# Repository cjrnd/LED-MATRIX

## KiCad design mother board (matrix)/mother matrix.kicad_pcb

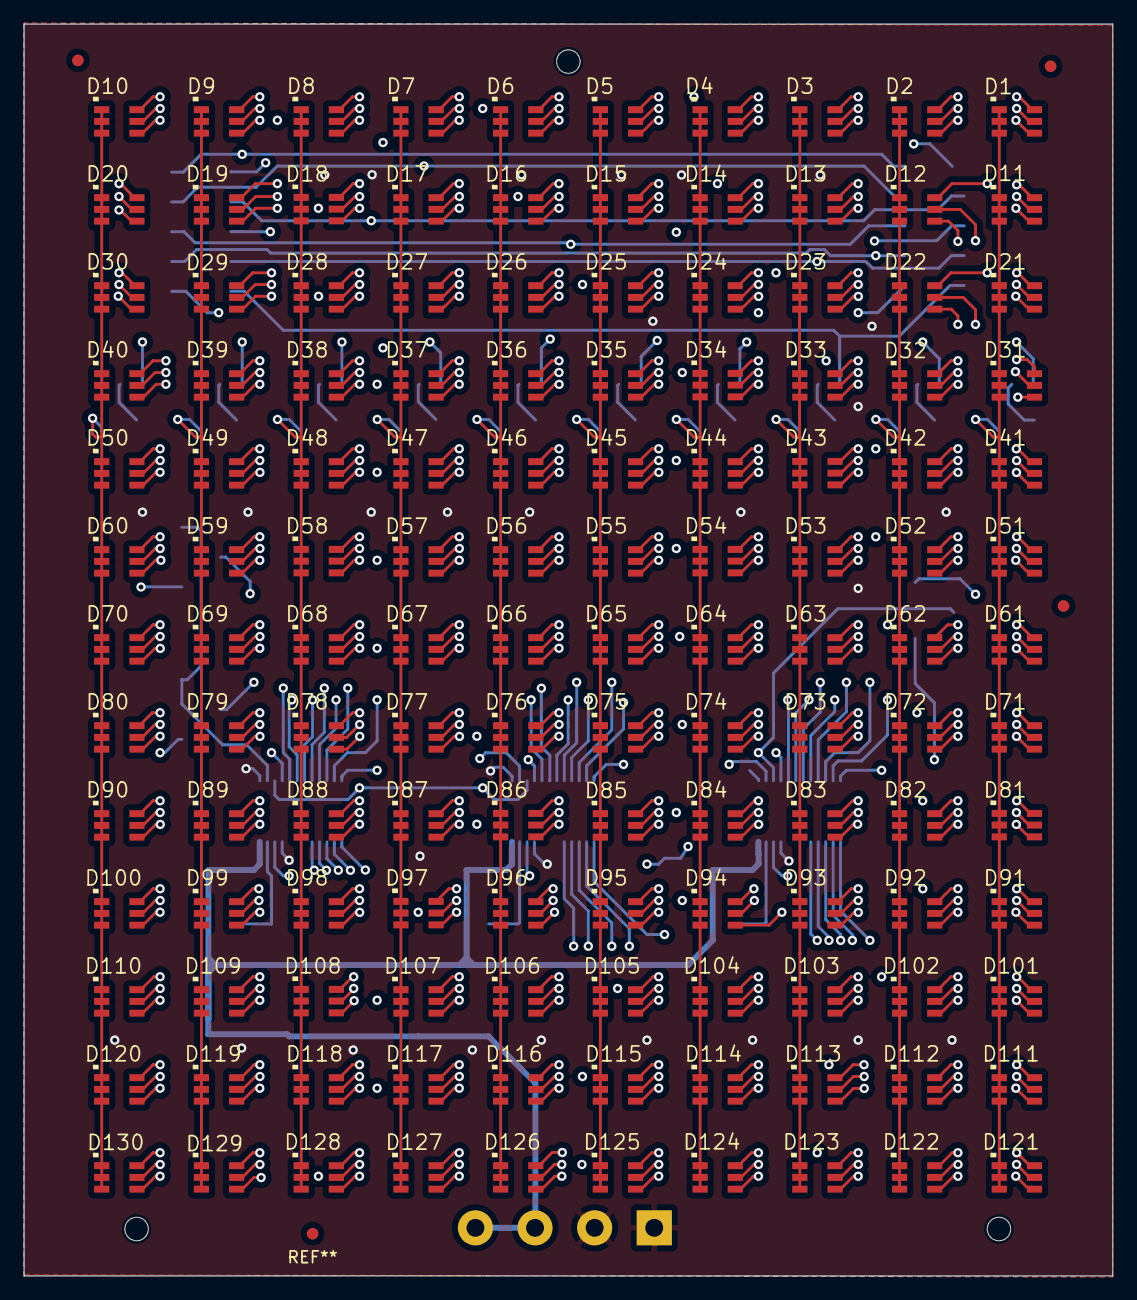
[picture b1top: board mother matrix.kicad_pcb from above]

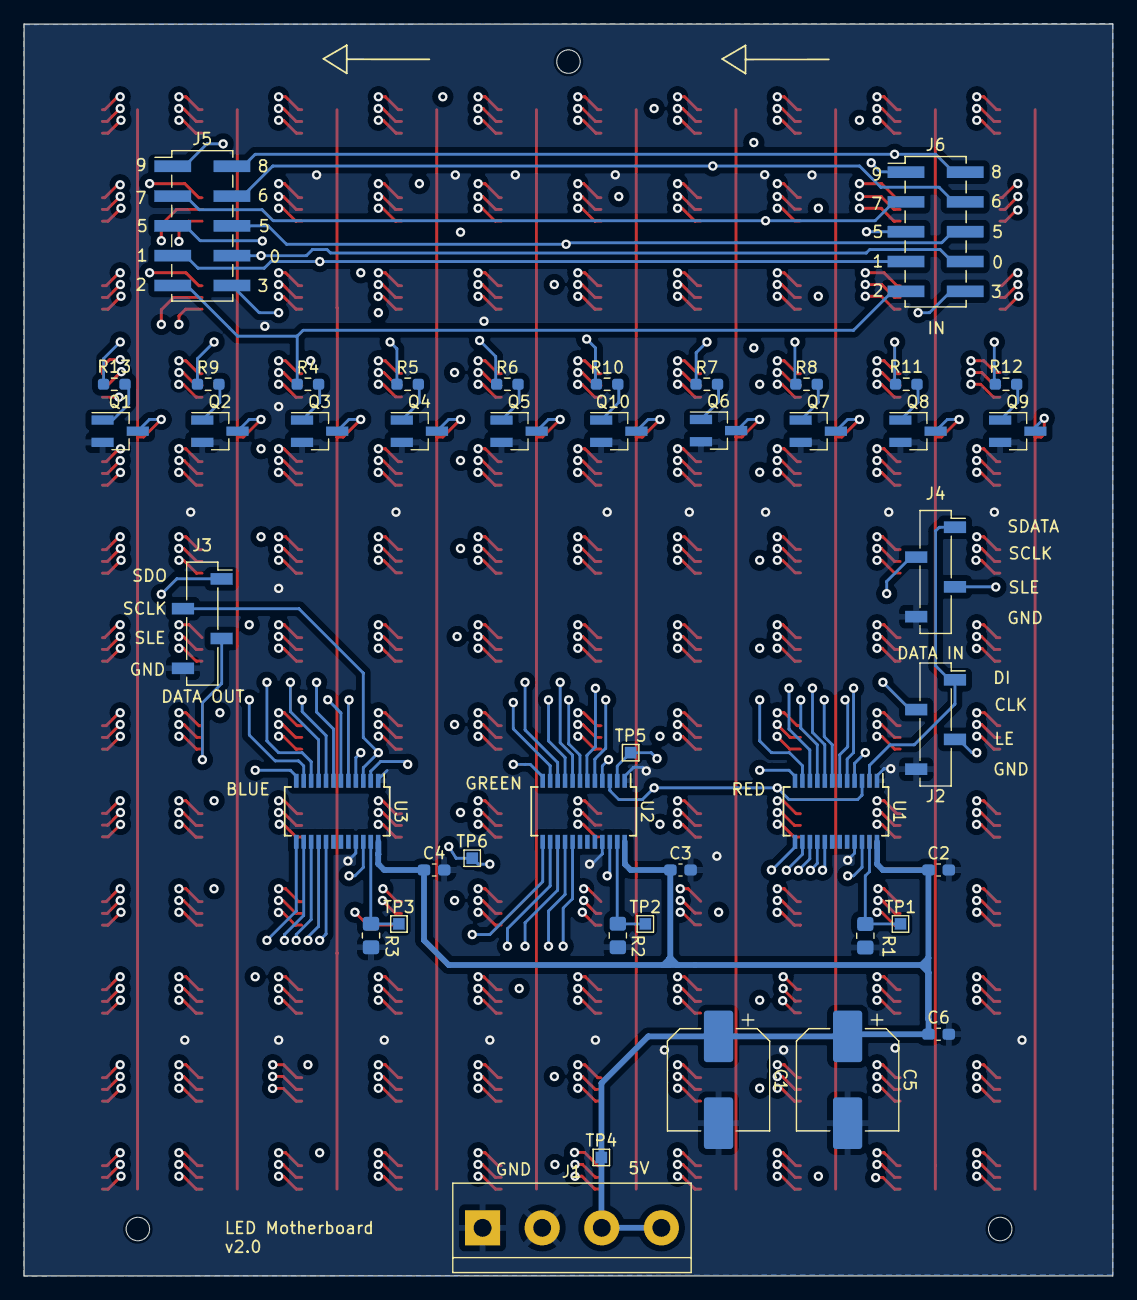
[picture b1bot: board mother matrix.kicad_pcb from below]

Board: 4 copper layers, 92.8 x 106.7 mm, 174 parts (44 on the bottom side), 80 nets.

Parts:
C1, C5: 220u; CP_Elec_8x10.5
C2, C3, C4, C6: 100n; C_0603_1608Metric_Pad1.08x0.95mm_HandSolder
D1, D2, D3, D4, D5, D6, D7, D8, D9, D10, D11, D12, D13, D14, D15, D16, D17, D18, D19, D20, D21, D22, D23, D24, D25, D26, D27, D28, D29, D30, D31, D32, D33, D34, D35, D36, D37, D38, D39, D40, D41, D42, D43, D44, D45, D46, D47, D48, D49, D50, D51, D52, D53, D54, D55, D56, D57, D58, D59, D60, D61, D62, D63, D64, D65, D66, D67, D68, D69, D70, D71, D72, D73, D74, D75, D76, D77, D78, D79, D80, D81, D82, D83, D84, D85, D86, D87, D88, D89, D90, D91, D92, D93, D94, D95, D96, D97, D98, D99, D100, D101, D102, D103, D104, D105, D106, D107, D108, D109, D110, D111, D112, D113, D114, D115, D116, D117, D118, D119, D120, D121, D122, D123, D124, D125, D126, D127, D128, D129, D130: LED_RGB; 3535_PLCC6
J1: POWER; TerminalBlock_bornier-4_P5.08mm
J2: DATA IN; PinSocket_1x04_P2.54mm_Vertical_SMD_Pin1Right
J3: DATA OUT; PinSocket_1x04_P2.54mm_Vertical_SMD_Pin1Right
J4: Serial_BUS; PinSocket_1x04_P2.54mm_Vertical_SMD_Pin1Right
J5: OUTPUT; PinHeader_2x05_P2.54mm_Vertical_SMD
J6: INPUT; PinHeader_2x05_P2.54mm_Vertical_SMD
Q1, Q2, Q3, Q4, Q5, Q6, Q7, Q8, Q9, Q10: PMV45EN2R; SOT-23_Handsoldering
R1: R_red; R_0805_2012Metric_Pad1.20x1.40mm_HandSolder
R2: R_green; R_0805_2012Metric_Pad1.20x1.40mm_HandSolder
R3: R_blue; R_0805_2012Metric_Pad1.20x1.40mm_HandSolder
R4, R5, R6, R7, R8, R9, R10, R11, R12, R13: 100; R_0603_1608Metric_Pad0.98x0.95mm_HandSolder
TP1, TP2, TP3, TP4, TP5, TP6: TestPoint; TestPoint_Pad_1.0x1.0mm
U1, U2, U3: SM16206; SSOP-24_3.9x8.7mm_P0.635mm

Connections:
+5V: C1.1, C2.1, C3.1, C4.1, C5.1, C6.1, J1.3, J1.4, TP4.1, U1.24 (VDD), U2.24 (VDD), U3.24 (VDD)
/Led/B_Row0: D1.4 (RA), D2.4 (RA), D3.4 (RA), D4.4 (RA), D5.4 (RA), D6.4 (RA), D7.4 (RA), D8.4 (RA), D9.4 (RA), D10.4 (RA), U3.5 (OUT0)
/Led/B_Row1: D11.4 (RA), D12.4 (RA), D13.4 (RA), D14.4 (RA), D15.4 (RA), D16.4 (RA), D17.4 (RA), D18.4 (RA), D19.4 (RA), D20.4 (RA), U3.6 (OUT1)
/Led/B_Row2: D21.4 (RA), D22.4 (RA), D23.4 (RA), D24.4 (RA), D25.4 (RA), D26.4 (RA), D27.4 (RA), D28.4 (RA), D29.4 (RA), D30.4 (RA), U3.7 (OUT2)
/Led/B_Row3: D31.4 (RA), D32.4 (RA), D33.4 (RA), D34.4 (RA), D35.4 (RA), D36.4 (RA), D37.4 (RA), D38.4 (RA), D39.4 (RA), D40.4 (RA), U3.8 (OUT3)
/Led/B_Row4: D41.4 (RA), D42.4 (RA), D43.4 (RA), D44.4 (RA), D45.4 (RA), D46.4 (RA), D47.4 (RA), D48.4 (RA), D49.4 (RA), D50.4 (RA), U3.9 (OUT4)
/Led/B_Row5: D51.4 (RA), D52.4 (RA), D53.4 (RA), D54.4 (RA), D55.4 (RA), D56.4 (RA), D57.4 (RA), D58.4 (RA), D59.4 (RA), D60.4 (RA), U3.10 (OUT5)
/Led/B_Row6: D61.4 (RA), D62.4 (RA), D63.4 (RA), D64.4 (RA), D65.4 (RA), D66.4 (RA), D67.4 (RA), D68.4 (RA), D69.4 (RA), D70.4 (RA), U3.11 (OUT6)
/Led/B_Row7: D71.4 (RA), D72.4 (RA), D73.4 (RA), D74.4 (RA), D75.4 (RA), D76.4 (RA), D77.4 (RA), D78.4 (RA), D79.4 (RA), D80.4 (RA), U3.12 (OUT7)
/Led/B_Row8: D81.4 (RA), D82.4 (RA), D83.4 (RA), D84.4 (RA), D85.4 (RA), D86.4 (RA), D87.4 (RA), D88.4 (RA), D89.4 (RA), D90.4 (RA), U3.13 (OUT8)
/Led/B_Row9: D91.4 (RA), D92.4 (RA), D93.4 (RA), D94.4 (RA), D95.4 (RA), D96.4 (RA), D97.4 (RA), D98.4 (RA), D99.4 (RA), D100.4 (RA), U3.14 (OUT9)
/Led/B_Row10: D101.4 (RA), D102.4 (RA), D103.4 (RA), D104.4 (RA), D105.4 (RA), D106.4 (RA), D107.4 (RA), D108.4 (RA), D109.4 (RA), D110.4 (RA), U3.15 (OUT10)
/Led/B_Row11: D111.4 (RA), D112.4 (RA), D113.4 (RA), D114.4 (RA), D115.4 (RA), D116.4 (RA), D117.4 (RA), D118.4 (RA), D119.4 (RA), D120.4 (RA), U3.16 (OUT11)
/Led/B_Row12: D121.4 (RA), D122.4 (RA), D123.4 (RA), D124.4 (RA), D125.4 (RA), D126.4 (RA), D127.4 (RA), D128.4 (RA), D129.4 (RA), D130.4 (RA), U3.17 (OUT12)
/Led/Col0: J5.8, J6.8, R13.1
/Led/Col1: J5.7, J6.7, R9.1
/Led/Col2: J5.9, J6.9, R4.1
/Led/Col3: J5.10, J6.10, R5.1
/Led/Col4: J5.5, J6.5, R6.1
/Led/Col5: J5.6, J6.6, R10.1
/Led/Col6: J5.4, J6.4, R7.1
/Led/Col7: J5.3, J6.3, R8.1
/Led/Col8: J5.2, J6.2, R11.2
/Led/Col9: J5.1, J6.1, R12.2
/Led/G_Row0: D1.5 (GA), D2.5 (GA), D3.5 (GA), D4.5 (GA), D5.5 (GA), D6.5 (GA), D7.5 (GA), D8.5 (GA), D9.5 (GA), D10.5 (GA), U2.5 (OUT0)
/Led/G_Row1: D11.5 (GA), D12.5 (GA), D13.5 (GA), D14.5 (GA), D15.5 (GA), D16.5 (GA), D17.5 (GA), D18.5 (GA), D19.5 (GA), D20.5 (GA), U2.6 (OUT1)
/Led/G_Row2: D21.5 (GA), D22.5 (GA), D23.5 (GA), D24.5 (GA), D25.5 (GA), D26.5 (GA), D27.5 (GA), D28.5 (GA), D29.5 (GA), D30.5 (GA), U2.7 (OUT2)
/Led/G_Row3: D31.5 (GA), D32.5 (GA), D33.5 (GA), D34.5 (GA), D35.5 (GA), D36.5 (GA), D37.5 (GA), D38.5 (GA), D39.5 (GA), D40.5 (GA), U2.8 (OUT3)
/Led/G_Row4: D41.5 (GA), D42.5 (GA), D43.5 (GA), D44.5 (GA), D45.5 (GA), D46.5 (GA), D47.5 (GA), D48.5 (GA), D49.5 (GA), D50.5 (GA), U2.9 (OUT4)
/Led/G_Row5: D51.5 (GA), D52.5 (GA), D53.5 (GA), D54.5 (GA), D55.5 (GA), D56.5 (GA), D57.5 (GA), D58.5 (GA), D59.5 (GA), D60.5 (GA), U2.10 (OUT5)
/Led/G_Row6: D61.5 (GA), D62.5 (GA), D63.5 (GA), D64.5 (GA), D65.5 (GA), D66.5 (GA), D67.5 (GA), D68.5 (GA), D69.5 (GA), D70.5 (GA), U2.11 (OUT6)
/Led/G_Row7: D71.5 (GA), D72.5 (GA), D73.5 (GA), D74.5 (GA), D75.5 (GA), D76.5 (GA), D77.5 (GA), D78.5 (GA), D79.5 (GA), D80.5 (GA), U2.12 (OUT7)
/Led/G_Row8: D81.5 (GA), D82.5 (GA), D83.5 (GA), D84.5 (GA), D85.5 (GA), D86.5 (GA), D87.5 (GA), D88.5 (GA), D89.5 (GA), D90.5 (GA), U2.13 (OUT8)
/Led/G_Row9: D91.5 (GA), D92.5 (GA), D93.5 (GA), D94.5 (GA), D95.5 (GA), D96.5 (GA), D97.5 (GA), D98.5 (GA), D99.5 (GA), D100.5 (GA), U2.14 (OUT9)
/Led/G_Row10: D101.5 (GA), D102.5 (GA), D103.5 (GA), D104.5 (GA), D105.5 (GA), D106.5 (GA), D107.5 (GA), D108.5 (GA), D109.5 (GA), D110.5 (GA), U2.15 (OUT10)
/Led/G_Row11: D111.5 (GA), D112.5 (GA), D113.5 (GA), D114.5 (GA), D115.5 (GA), D116.5 (GA), D117.5 (GA), D118.5 (GA), D119.5 (GA), D120.5 (GA), U2.16 (OUT11)
/Led/G_Row12: D121.5 (GA), D122.5 (GA), D123.5 (GA), D124.5 (GA), D125.5 (GA), D126.5 (GA), D127.5 (GA), D128.5 (GA), D129.5 (GA), D130.5 (GA), U2.17 (OUT12)
/Led/R_Row0: D1.6 (BA), D2.6 (BA), D3.6 (BA), D4.6 (BA), D5.6 (BA), D6.6 (BA), D7.6 (BA), D8.6 (BA), D9.6 (BA), D10.6 (BA), U1.5 (OUT0)
/Led/R_Row1: D11.6 (BA), D12.6 (BA), D13.6 (BA), D14.6 (BA), D15.6 (BA), D16.6 (BA), D17.6 (BA), D18.6 (BA), D19.6 (BA), D20.6 (BA), U1.6 (OUT1)
/Led/R_Row2: D21.6 (BA), D22.6 (BA), D23.6 (BA), D24.6 (BA), D25.6 (BA), D26.6 (BA), D27.6 (BA), D28.6 (BA), D29.6 (BA), D30.6 (BA), U1.7 (OUT2)
/Led/R_Row3: D31.6 (BA), D32.6 (BA), D33.6 (BA), D34.6 (BA), D35.6 (BA), D36.6 (BA), D37.6 (BA), D38.6 (BA), D39.6 (BA), D40.6 (BA), U1.8 (OUT3)
/Led/R_Row4: D41.6 (BA), D42.6 (BA), D43.6 (BA), D44.6 (BA), D45.6 (BA), D46.6 (BA), D47.6 (BA), D48.6 (BA), D49.6 (BA), D50.6 (BA), U1.9 (OUT4)
/Led/R_Row5: D51.6 (BA), D52.6 (BA), D53.6 (BA), D54.6 (BA), D55.6 (BA), D56.6 (BA), D57.6 (BA), D58.6 (BA), D59.6 (BA), D60.6 (BA), U1.10 (OUT5)
/Led/R_Row6: D61.6 (BA), D62.6 (BA), D63.6 (BA), D64.6 (BA), D65.6 (BA), D66.6 (BA), D67.6 (BA), D68.6 (BA), D69.6 (BA), D70.6 (BA), U1.11 (OUT6)
/Led/R_Row7: D71.6 (BA), D72.6 (BA), D73.6 (BA), D74.6 (BA), D75.6 (BA), D76.6 (BA), D77.6 (BA), D78.6 (BA), D79.6 (BA), D80.6 (BA), U1.12 (OUT7)
/Led/R_Row8: D81.6 (BA), D82.6 (BA), D83.6 (BA), D84.6 (BA), D85.6 (BA), D86.6 (BA), D87.6 (BA), D88.6 (BA), D89.6 (BA), D90.6 (BA), U1.13 (OUT8)
/Led/R_Row9: D91.6 (BA), D92.6 (BA), D93.6 (BA), D94.6 (BA), D95.6 (BA), D96.6 (BA), D97.6 (BA), D98.6 (BA), D99.6 (BA), D100.6 (BA), U1.14 (OUT9)
/Led/R_Row10: D101.6 (BA), D102.6 (BA), D103.6 (BA), D104.6 (BA), D105.6 (BA), D106.6 (BA), D107.6 (BA), D108.6 (BA), D109.6 (BA), D110.6 (BA), U1.15 (OUT10)
/Led/R_Row11: D111.6 (BA), D112.6 (BA), D113.6 (BA), D114.6 (BA), D115.6 (BA), D116.6 (BA), D117.6 (BA), D118.6 (BA), D119.6 (BA), D120.6 (BA), U1.16 (OUT11)
/Led/R_Row12: D121.6 (BA), D122.6 (BA), D123.6 (BA), D124.6 (BA), D125.6 (BA), D126.6 (BA), D127.6 (BA), D128.6 (BA), D129.6 (BA), D130.6 (BA), U1.17 (OUT12)
/Logic/R_Bset: R3.1, TP3.1, U3.23 (R-EXT)
/Logic/R_Gset: R2.1, TP2.1, U2.23 (R-EXT)
/Logic/R_Rset: R1.1, TP1.1, U1.23 (R-EXT)
GND: C1.2, C2.2, C3.2, C4.2, C5.2, C6.2, J1.1, J1.2, J2.4, J3.4, J4.4, Q1.2 (S), Q2.2 (S), Q3.2 (S), Q4.2 (S), Q5.2 (S), Q6.2 (S), Q7.2 (S), Q8.2 (S), Q9.2 (S), Q10.2 (S), R1.2, R2.2, R3.2, U1.1 (GND), U1.21 (~OE), U2.1 (GND), U2.21 (~OE), U3.1 (GND), U3.21 (~OE)
unnamed: D1.1 (RK), D1.2 (GK), D1.3 (BK), D11.1 (RK), D11.2 (GK), D11.3 (BK), D21.1 (RK), D21.2 (GK), D21.3 (BK), D31.1 (RK), D31.2 (GK), D31.3 (BK), D41.1 (RK), D41.2 (GK), D41.3 (BK), D51.1 (RK), D51.2 (GK), D51.3 (BK), D61.1 (RK), D61.2 (GK), D61.3 (BK), D71.1 (RK), D71.2 (GK), D71.3 (BK), D81.1 (RK), D81.2 (GK), D81.3 (BK), D91.1 (RK), D91.2 (GK), D91.3 (BK), D101.1 (RK), D101.2 (GK), D101.3 (BK), D111.1 (RK), D111.2 (GK), D111.3 (BK), D121.1 (RK), D121.2 (GK), D121.3 (BK), Q1.3 (D)
unnamed: D10.1 (RK), D10.2 (GK), D10.3 (BK), D20.1 (RK), D20.2 (GK), D20.3 (BK), D30.1 (RK), D30.2 (GK), D30.3 (BK), D40.1 (RK), D40.2 (GK), D40.3 (BK), D50.1 (RK), D50.2 (GK), D50.3 (BK), D60.1 (RK), D60.2 (GK), D60.3 (BK), D70.1 (RK), D70.2 (GK), D70.3 (BK), D80.1 (RK), D80.2 (GK), D80.3 (BK), D90.1 (RK), D90.2 (GK), D90.3 (BK), D100.1 (RK), D100.2 (GK), D100.3 (BK), D110.1 (RK), D110.2 (GK), D110.3 (BK), D120.1 (RK), D120.2 (GK), D120.3 (BK), D130.1 (RK), D130.2 (GK), D130.3 (BK), Q9.3 (D)
unnamed: D2.1 (RK), D2.2 (GK), D2.3 (BK), D12.1 (RK), D12.2 (GK), D12.3 (BK), D22.1 (RK), D22.2 (GK), D22.3 (BK), D32.1 (RK), D32.2 (GK), D32.3 (BK), D42.1 (RK), D42.2 (GK), D42.3 (BK), D52.1 (RK), D52.2 (GK), D52.3 (BK), D62.1 (RK), D62.2 (GK), D62.3 (BK), D72.1 (RK), D72.2 (GK), D72.3 (BK), D82.1 (RK), D82.2 (GK), D82.3 (BK), D92.1 (RK), D92.2 (GK), D92.3 (BK), D102.1 (RK), D102.2 (GK), D102.3 (BK), D112.1 (RK), D112.2 (GK), D112.3 (BK), D122.1 (RK), D122.2 (GK), D122.3 (BK), Q2.3 (D)
unnamed: D3.1 (RK), D3.2 (GK), D3.3 (BK), D13.1 (RK), D13.2 (GK), D13.3 (BK), D23.1 (RK), D23.2 (GK), D23.3 (BK), D33.1 (RK), D33.2 (GK), D33.3 (BK), D43.1 (RK), D43.2 (GK), D43.3 (BK), D53.1 (RK), D53.2 (GK), D53.3 (BK), D63.1 (RK), D63.2 (GK), D63.3 (BK), D73.1 (RK), D73.2 (GK), D73.3 (BK), D83.1 (RK), D83.2 (GK), D83.3 (BK), D93.1 (RK), D93.2 (GK), D93.3 (BK), D103.1 (RK), D103.2 (GK), D103.3 (BK), D113.1 (RK), D113.2 (GK), D113.3 (BK), D123.1 (RK), D123.2 (GK), D123.3 (BK), Q3.3 (D)
unnamed: D4.1 (RK), D4.2 (GK), D4.3 (BK), D14.1 (RK), D14.2 (GK), D14.3 (BK), D24.1 (RK), D24.2 (GK), D24.3 (BK), D34.1 (RK), D34.2 (GK), D34.3 (BK), D44.1 (RK), D44.2 (GK), D44.3 (BK), D54.1 (RK), D54.2 (GK), D54.3 (BK), D64.1 (RK), D64.2 (GK), D64.3 (BK), D74.1 (RK), D74.2 (GK), D74.3 (BK), D84.1 (RK), D84.2 (GK), D84.3 (BK), D94.1 (RK), D94.2 (GK), D94.3 (BK), D104.1 (RK), D104.2 (GK), D104.3 (BK), D114.1 (RK), D114.2 (GK), D114.3 (BK), D124.1 (RK), D124.2 (GK), D124.3 (BK), Q4.3 (D)
unnamed: D5.1 (RK), D5.2 (GK), D5.3 (BK), D15.1 (RK), D15.2 (GK), D15.3 (BK), D25.1 (RK), D25.2 (GK), D25.3 (BK), D35.1 (RK), D35.2 (GK), D35.3 (BK), D45.1 (RK), D45.2 (GK), D45.3 (BK), D55.1 (RK), D55.2 (GK), D55.3 (BK), D65.1 (RK), D65.2 (GK), D65.3 (BK), D75.1 (RK), D75.2 (GK), D75.3 (BK), D85.1 (RK), D85.2 (GK), D85.3 (BK), D95.1 (RK), D95.2 (GK), D95.3 (BK), D105.1 (RK), D105.2 (GK), D105.3 (BK), D115.1 (RK), D115.2 (GK), D115.3 (BK), D125.1 (RK), D125.2 (GK), D125.3 (BK), Q5.3 (D)
unnamed: D6.1 (RK), D6.2 (GK), D6.3 (BK), D16.1 (RK), D16.2 (GK), D16.3 (BK), D26.1 (RK), D26.2 (GK), D26.3 (BK), D36.1 (RK), D36.2 (GK), D36.3 (BK), D46.1 (RK), D46.2 (GK), D46.3 (BK), D56.1 (RK), D56.2 (GK), D56.3 (BK), D66.1 (RK), D66.2 (GK), D66.3 (BK), D76.1 (RK), D76.2 (GK), D76.3 (BK), D86.1 (RK), D86.2 (GK), D86.3 (BK), D96.1 (RK), D96.2 (GK), D96.3 (BK), D106.1 (RK), D106.2 (GK), D106.3 (BK), D116.1 (RK), D116.2 (GK), D116.3 (BK), D126.1 (RK), D126.2 (GK), D126.3 (BK), Q10.3 (D)
unnamed: D7.1 (RK), D7.2 (GK), D7.3 (BK), D17.1 (RK), D17.2 (GK), D17.3 (BK), D27.1 (RK), D27.2 (GK), D27.3 (BK), D37.1 (RK), D37.2 (GK), D37.3 (BK), D47.1 (RK), D47.2 (GK), D47.3 (BK), D57.1 (RK), D57.2 (GK), D57.3 (BK), D67.1 (RK), D67.2 (GK), D67.3 (BK), D77.1 (RK), D77.2 (GK), D77.3 (BK), D87.1 (RK), D87.2 (GK), D87.3 (BK), D97.1 (RK), D97.2 (GK), D97.3 (BK), D107.1 (RK), D107.2 (GK), D107.3 (BK), D117.1 (RK), D117.2 (GK), D117.3 (BK), D127.1 (RK), D127.2 (GK), D127.3 (BK), Q6.3 (D)
unnamed: D8.1 (RK), D8.2 (GK), D8.3 (BK), D18.1 (RK), D18.2 (GK), D18.3 (BK), D28.1 (RK), D28.2 (GK), D28.3 (BK), D38.1 (RK), D38.2 (GK), D38.3 (BK), D48.1 (RK), D48.2 (GK), D48.3 (BK), D58.1 (RK), D58.2 (GK), D58.3 (BK), D68.1 (RK), D68.2 (GK), D68.3 (BK), D78.1 (RK), D78.2 (GK), D78.3 (BK), D88.1 (RK), D88.2 (GK), D88.3 (BK), D98.1 (RK), D98.2 (GK), D98.3 (BK), D108.1 (RK), D108.2 (GK), D108.3 (BK), D118.1 (RK), D118.2 (GK), D118.3 (BK), D128.1 (RK), D128.2 (GK), D128.3 (BK), Q7.3 (D)
unnamed: D9.1 (RK), D9.2 (GK), D9.3 (BK), D19.1 (RK), D19.2 (GK), D19.3 (BK), D29.1 (RK), D29.2 (GK), D29.3 (BK), D39.1 (RK), D39.2 (GK), D39.3 (BK), D49.1 (RK), D49.2 (GK), D49.3 (BK), D59.1 (RK), D59.2 (GK), D59.3 (BK), D69.1 (RK), D69.2 (GK), D69.3 (BK), D79.1 (RK), D79.2 (GK), D79.3 (BK), D89.1 (RK), D89.2 (GK), D89.3 (BK), D99.1 (RK), D99.2 (GK), D99.3 (BK), D109.1 (RK), D109.2 (GK), D109.3 (BK), D119.1 (RK), D119.2 (GK), D119.3 (BK), D129.1 (RK), D129.2 (GK), D129.3 (BK), Q8.3 (D)
unnamed: Q1.1 (G), R13.2
unnamed: Q2.1 (G), R9.2
unnamed: Q3.1 (G), R4.2
unnamed: Q4.1 (G), R5.2
unnamed: Q5.1 (G), R6.2
unnamed: Q6.1 (G), R7.2
unnamed: Q7.1 (G), R8.2
unnamed: Q8.1 (G), R11.1
unnamed: Q9.1 (G), R12.1
unnamed: Q10.1 (G), R10.2
unnamed: TP5.1, U1.22 (SDO), U2.2 (SDI)
unnamed: TP6.1, U2.22 (SDO), U3.2 (SDI)
SDO: J3.1, U3.22 (SDO)
S_CLK: J2.2, J3.2, J4.2, U1.3 (CLK), U2.3 (CLK), U3.3 (CLK)
S_DATA: J2.1, J4.1, U1.2 (SDI)
S_LE: J2.3, J3.3, J4.3, U1.4 (LE), U2.4 (LE), U3.4 (LE)

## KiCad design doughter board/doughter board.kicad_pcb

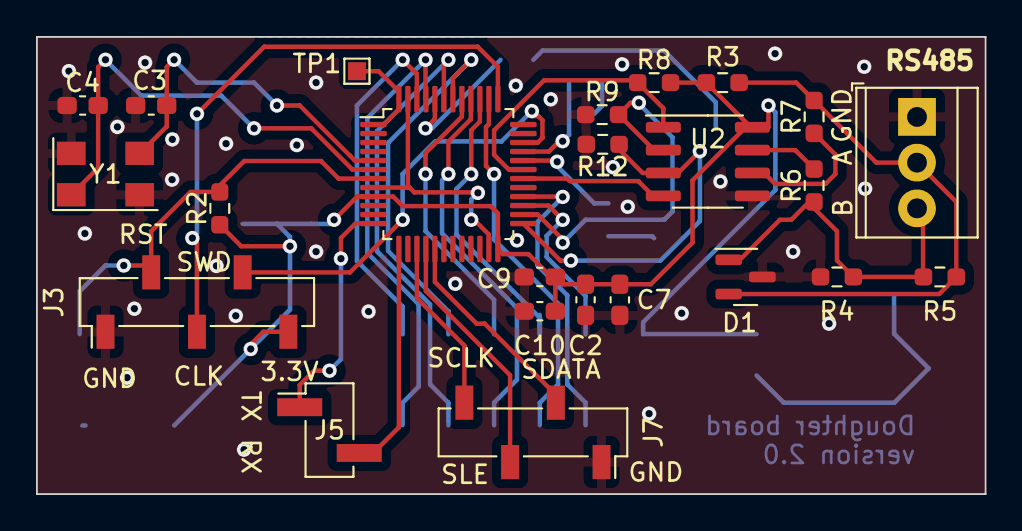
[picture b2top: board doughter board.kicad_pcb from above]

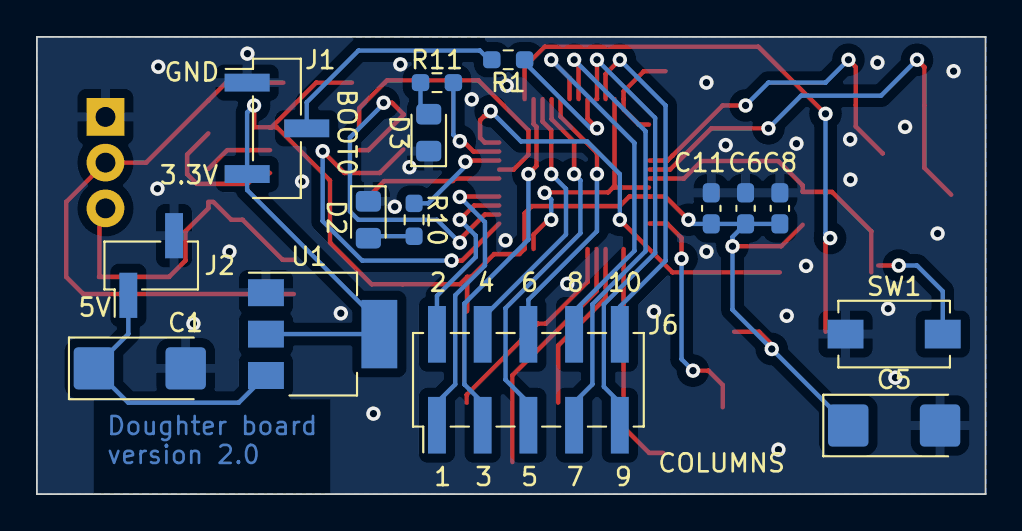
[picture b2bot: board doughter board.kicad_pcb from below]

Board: 2 copper layers, 52.7 x 25.4 mm, 39 parts (15 on the bottom side), 39 nets.

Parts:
C1, C5: 10u; CP_EIA-6032-28_Kemet-C_Pad2.25x2.35mm_HandSolder
C2, C6, C7, C8: 100n; C_0603_1608Metric_Pad1.08x0.95mm_HandSolder
C3, C4: 20p; C_0603_1608Metric_Pad1.08x0.95mm_HandSolder
C9: 1u; C_0603_1608Metric_Pad1.08x0.95mm_HandSolder
C10: 10n; C_0603_1608Metric_Pad1.08x0.95mm_HandSolder
C11: 4.7u; C_0603_1608Metric_Pad1.08x0.95mm_HandSolder
D1: SM712_SOT23; SOT-23
D2: Green; LED_0805_2012Metric_Pad1.15x1.40mm_HandSolder
D3: Red; LED_0805_2012Metric_Pad1.15x1.40mm_HandSolder
J1: BOOT_TO/ SELECTOR; PinHeader_1x03_P2.54mm_Vertical_SMD_Pin1Left
J2: BOOT_TO/ SELECTOR; PinHeader_1x02_P2.54mm_Vertical_SMD_Pin1Left
J3: Conn_01x05; PinSocket_1x05_P2.54mm_Vertical_SMD_Pin1Left
J4: RS 485; TerminalBlock_TE_282834-3_1x03_P2.54mm_Horizontal
J5: UART2; PinHeader_1x02_P2.54mm_Vertical_SMD_Pin1Left
J6: OUTPUT; PinHeader_2x05_P2.54mm_Vertical_SMD
J7: Serial_BUS; PinSocket_1x04_P2.54mm_Vertical_SMD_Pin1Right
R1, R2, R8, R9, R12: 10k; R_0603_1608Metric_Pad0.98x0.95mm_HandSolder
R3, R4: 360; R_0603_1608Metric_Pad0.98x0.95mm_HandSolder
R5: 120; R_0603_1608Metric_Pad0.98x0.95mm_HandSolder
R6, R7: 10; R_0603_1608Metric_Pad0.98x0.95mm_HandSolder
R10: 510; R_0603_1608Metric_Pad0.98x0.95mm_HandSolder
R11: 680; R_0603_1608Metric_Pad0.98x0.95mm_HandSolder
SW1: SW_SPST; SW_SPST_EVQPE1
TP1: TestPoint; TestPoint_Pad_1.0x1.0mm
U1: LM1117-3.3; SOT-223
U2: SN65HVD11; SOIC-8_3.9x4.9mm_P1.27mm
U3: STM32F030C6Tx; LQFP-48_7x7mm_P0.5mm
Y1: 8 MHz; Crystal_SMD_Abracon_ABM3C-4Pin_5.0x3.2mm

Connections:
+5V: C1.1, J2.1, U1.3 (VI)
/A: D1.2 (A2), J4.2, R3.2, R5.2, R7.1
/B: D1.1 (A1), J4.3, R4.1, R5.1, R6.1
/Col0: J6.8, U3.42 (PB6)
/Col1: J6.7, U3.43 (PB7)
/Col2: J6.9, U3.45 (PB8)
/Col3: J6.10, U3.46 (PB9)
/Col4: J6.5, U3.40 (PB4)
/Col5: J6.6, U3.41 (PB5)
/Col6: J6.4, U3.39 (PB3)
/Col7: J6.3, U3.38 (PA15)
/Col8: J6.2, U3.27 (PB14)
/Col9: J6.1, U3.28 (PB15)
/S_CLK: J7.4, U3.15 (PA5)
/S_DATA: J7.2, U3.17 (PA7)
/S_LE: J7.3, U3.16 (PA6)
/UART2_RX: J5.2, U3.13 (PA3)
/UART2_TX: J5.1, U3.12 (PA2)
BOOT0: R1.1, U3.44 (BOOT0)
DE: R12.1, U2.3 (DE), U3.25 (PB12)
GND: C1.2, C2.2, C3.1, C4.1, C5.2, C6.2, C7.2, C8.2, C9.2, C10.2, C11.2, D1.3 (common), D2.1 (K), D3.1 (K), J1.1, J2.2, J3.1, J4.1, J7.1, R4.2, R9.2, R12.2, SW1.1 (A), U1.1 (GND), U2.5 (GND), Y1.2 (GND), Y1.4 (GND)
LED_debug1: R10.1, U3.32 (PA11)
LED_debug2: R11.1, U3.33 (PA12)
unnamed: D2.2 (A), R10.2
unnamed: D3.2 (A), R11.2
unnamed: J1.2, R1.2
unnamed: TP1.1, U3.1 (VDD), U3.48 (VDD)
unnamed: R7.2, U2.6 (A)
unnamed: R6.2, U2.7 (B)
unnamed: U3.8 (VSSA), U3.23 (VSS), U3.47 (VSS)
RST: J3.2, R2.2, SW1.2 (B), U3.7 (NRST)
SWD_CLK: J3.3, U3.37 (PA14)
SWD_O: J3.4, U3.34 (PA13)
UART1_RX_R: R8.2, U2.1 (R), U3.31 (PA10)
UART1_TX_D: U2.4 (D), U3.30 (PA9)
VDD: C2.1, C5.1, C6.1, C7.1, C8.1, C9.1, C10.1, C11.1, J1.3, J3.5, R2.1, R3.1, R8.1, U1.2 (VO), U1.4 (VO), U2.8 (VCC), U3.9 (VDDA), U3.24 (VDD)
Xtal_IN: C3.2, U3.5 (PF0), Y1.3
Xtal_OUT: C4.2, U3.6 (PF1), Y1.1
~RE: R9.1, U2.2 (~RE), U3.26 (PB13)
